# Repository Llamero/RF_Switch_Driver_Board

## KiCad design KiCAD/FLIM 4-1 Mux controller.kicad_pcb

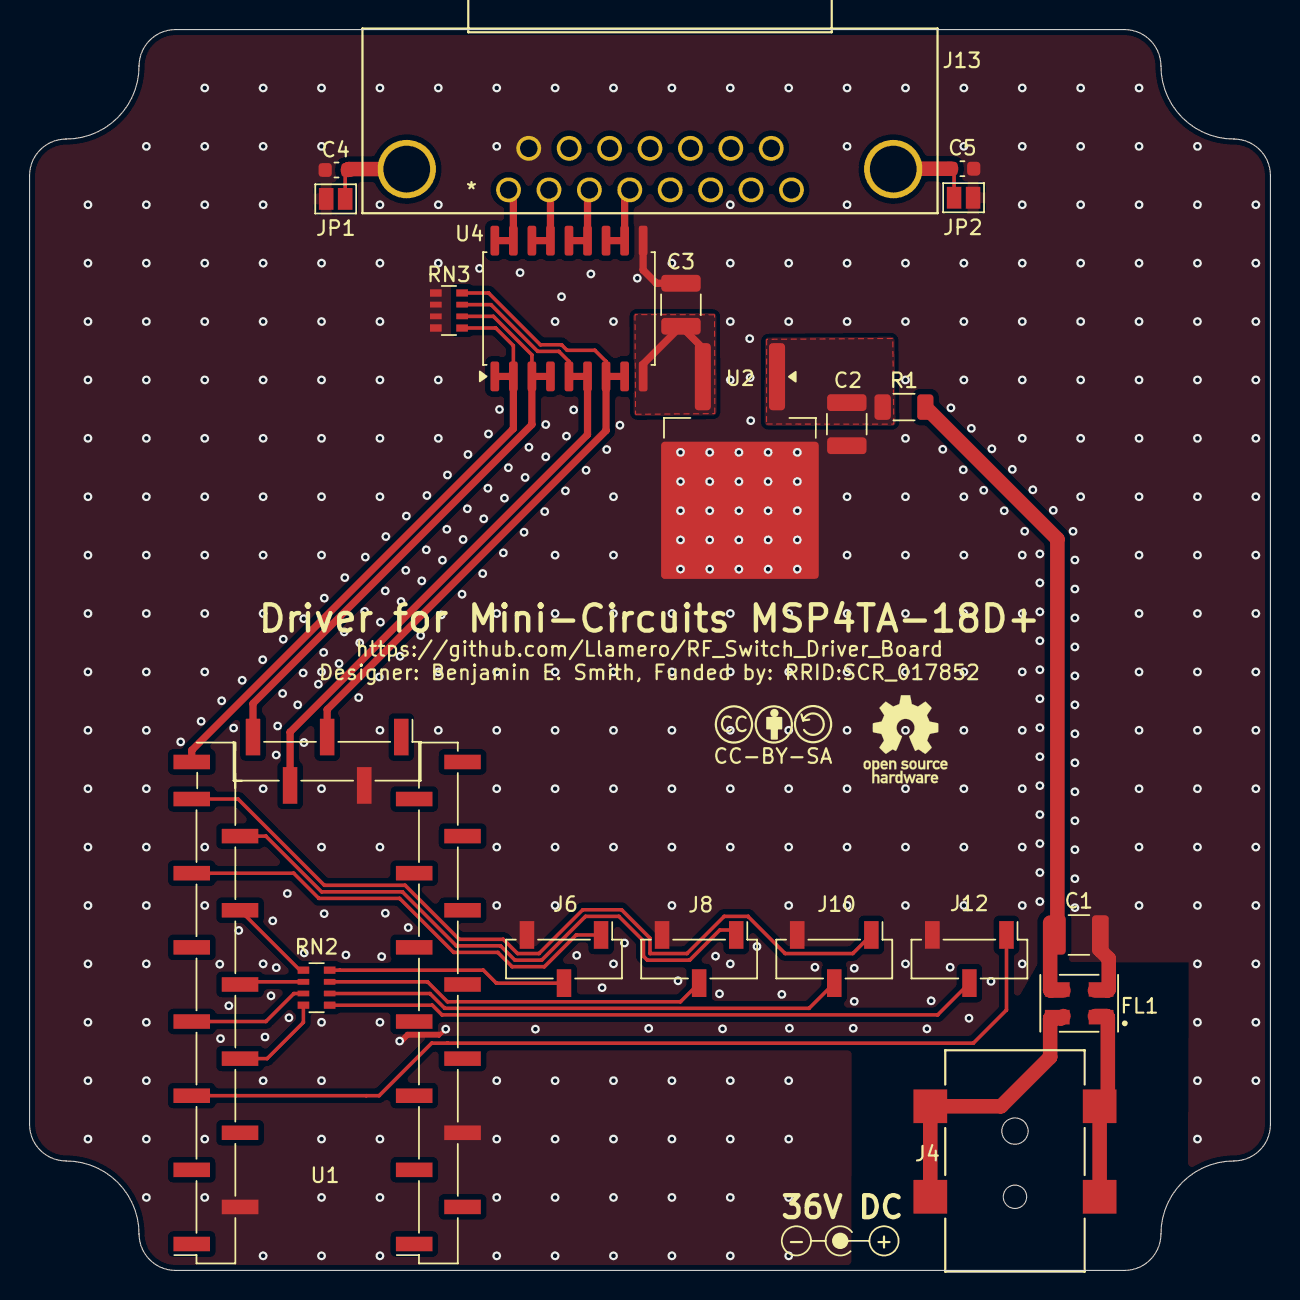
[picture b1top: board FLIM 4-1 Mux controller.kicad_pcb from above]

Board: 2 copper layers, 85.0 x 85.0 mm, 23 parts (0 on the bottom side), 27 nets.

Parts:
C1, C2, C3: 4.7µF; C_1210_3225Metric
C4, C5: 3.3 nF; C_0603_1608Metric
FL1: DLW5ATN272SQ2L; FIL_DLW5ATN272SQ2L
J4: Barrel_Jack; CONN4_00164_TEN
J6, J8, J10, J12: Conn_01x03_Socket; PinSocket_1x03_P2.54mm_Vertical_SMD_Pin1Left
J13: DB15; CONN_182-015-213R531_NRC
JP1, JP2: Jumper_2_Open; SolderJumper-2_P1.3mm_Open_Pad1.0x1.5mm
R1: 50; R_1206_3216Metric
RN2, RN3: 1k; R_Array_Convex_4x0603
SYM1: Logo_Open_Hardware_Small; CC-BY-SA Symbol
SYM2: Logo_Open_Hardware_Small; OSHW-Logo_5.7x6mm_SilkScreen
SYM3: Logo_Center_Positive; Polarity
U1: Itsy_Bitsy_32u4; Itsy Bitsy 32u4 with headers
U2: 24V LDO; TO-263-2
U4: TBD62783A; SOIC-18W_7.5x11.6mm_P1.27mm

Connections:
+24V: C3.1, U2.3 (OUT), U4.9 (VCC)
+36V: FL1.4, J4.1
/Button1: J6.1, U1.23 (~3_SCL)
/Button2: J8.1, U1.22 (2_SDA)
/Button3: J10.1, U1.21 (1_TX)
/Button4: J12.1, U1.29 (12_A11)
/LED1: RN2.1 (R1.1), U1.24 (~5)
/LED2: RN2.2 (R2.1), U1.26 (~9_A9)
/LED3: RN2.3 (R3.1), U1.27 (~10_A10)
/LED4: RN2.4 (R4.1), U1.28 (~11)
/Relay 1: J13.1, U4.17 (O2), U4.18 (O1)
/Relay 2: J13.2, U4.15 (O4), U4.16 (O3)
/Relay 3: J13.3, U4.13 (O6), U4.14 (O5)
/Relay 4: J13.4, U4.11 (O8), U4.12 (O7)
/SW1: RN3.1 (R1.1), U1.20 (0_RX), U4.1 (I1), U4.2 (I2)
/SW2: RN3.2 (R2.1), U1.19 (4_A6), U4.3 (I3), U4.4 (I4)
/SW3: RN3.3 (R3.1), U1.18 (6_A7), U4.5 (I5), U4.6 (I6)
/SW4: RN3.4 (R4.1), U1.17 (8_A8), U4.7 (I7), U4.8 (I8)
GND: C1.2, C2.2, C3.2, C4.2, C5.2, FL1.2, J6.3, J8.3, J10.3, J12.3, J13.9, JP1.1 (A), JP2.1 (A), RN3.5 (R4.2), RN3.6 (R3.2), RN3.7 (R2.2), RN3.8 (R1.2), U1.4 (GND), U1.16 (Gnd), U1.32 (Gnd), U2.2 (GND), U4.10 (GND)
GNDPWR: FL1.1, J4.2
unnamed: C1.1, FL1.3, R1.2
unnamed: J6.2, RN2.8 (R1.2)
unnamed: J8.2, RN2.7 (R2.2)
unnamed: J10.2, RN2.6 (R3.2)
unnamed: J12.2, RN2.5 (R4.2)
unnamed: C4.1, C5.1, J13.SH (PAD), JP1.2 (B), JP2.2 (B)
unnamed: C2.1, R1.1, U2.1 (IN)
